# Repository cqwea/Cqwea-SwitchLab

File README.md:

# Cqwea SwitchLab

## About
cqwea switchlab is a calculator that does simple math problems and easy daily life problems as to why ive built it was I had enough with the other companies boring calculator designs and mushy buttons so ive built my own open case designed beautiful calculator with mechanic switches so its gonna be 10x better to press and do math at
## Features
MATH!
## Assembly

## Case

## Schematics

## PCB

## Aİ

Hey ima be honest i used ai to debug and make the placeholder code but the main code that ill srite when i got the device in hand is %100 hand written by me

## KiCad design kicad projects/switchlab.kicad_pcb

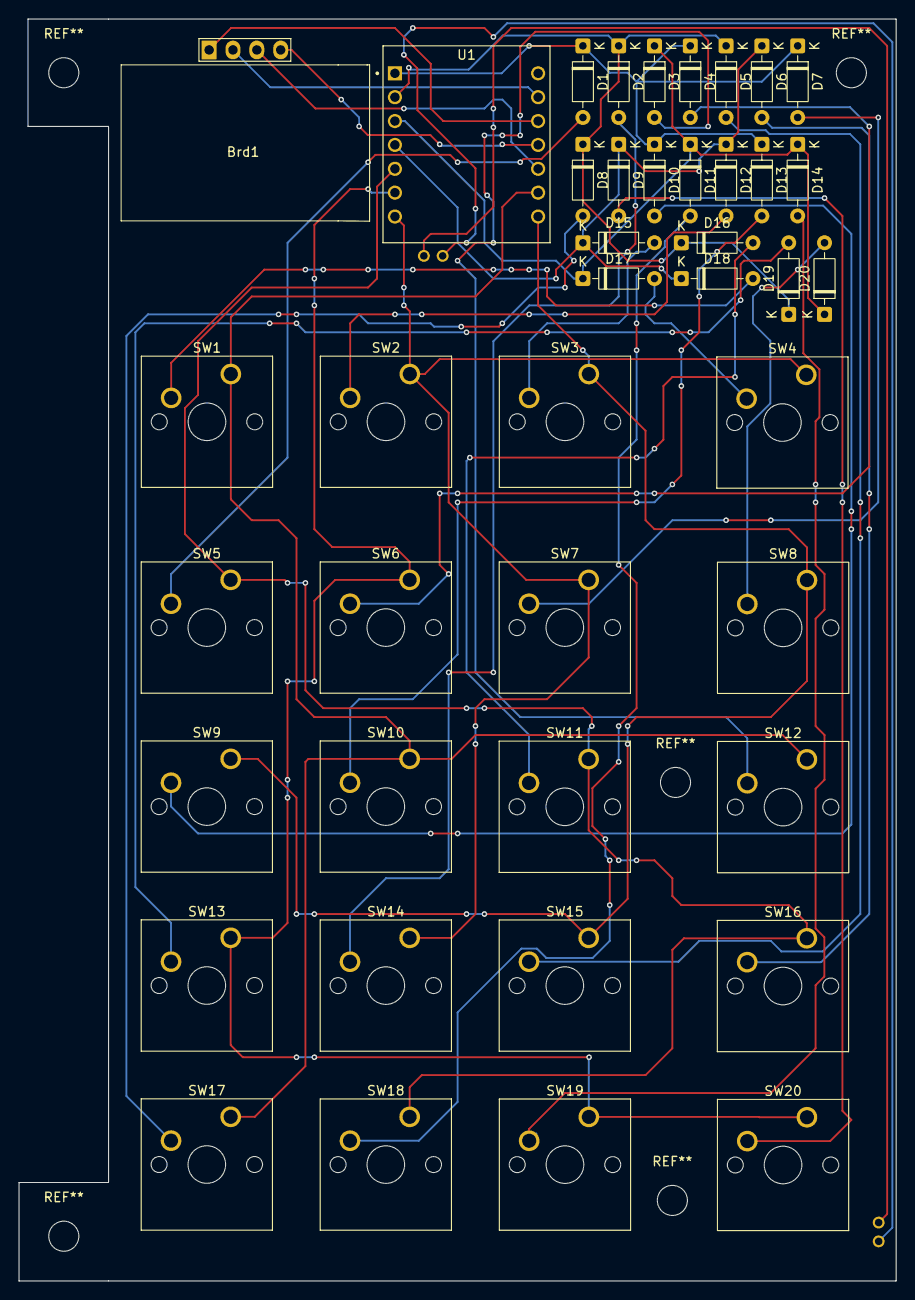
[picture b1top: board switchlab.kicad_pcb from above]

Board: 2 copper layers, 93.3 x 134.3 mm, 42 parts (0 on the bottom side), 33 nets.

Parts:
Brd1: SSD1306; 128x64OLED
D1, D2, D3, D4, D5, D6, D7, D8, D9, D10, D11, D12, D13, D14, D15, D16, D17, D18, D19, D20: 1N4148; D_DO-35_SOD27_P7.62mm_Horizontal
SW1, SW2, SW3, SW4, SW5, SW6, SW7, SW8, SW9, SW10, SW11, SW12, SW13, SW14, SW15, SW16, SW17, SW18, SW19, SW20: SW_Push; SW_Cherry_MX_1.00u_PCB
U1: XIAO_ESP32_S3; MODULE_XIAO_ESP32_S3

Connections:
/col1: SW5.1, SW11.1, SW16.1, SW18.1, U1.5 (D4/GPIO5)
/col2: SW6.1, SW13.1, SW19.1, SW20.1, U1.6 (D5/GPIO6)
/col3: SW2.1, SW4.1, SW7.1, SW14.1, U1.7 (D6/GPIO43)
/col4: SW3.1, SW8.1, SW9.1, SW15.1, U1.8 (D7/GPIO44)
/col5: SW1.1, SW10.1, SW12.1, SW17.1, U1.9 (D8/GPIO7)
/d7: Brd1.3 (SCL), U1.10 (D9/GPIO8)
/d8: Brd1.4 (SDA), U1.11 (D10/GPIO9)
/pwr: Brd1.1 (VCC), U1.12 (3V3)
/row1: D1.1 (K), D4.1 (K), D7.1 (K), D10.1 (K), D13.1 (K), U1.1 (D0/GPIO1)
/row2: D2.1 (K), D5.1 (K), D8.1 (K), D16.1 (K), D19.1 (K), U1.2 (D1/GPIO2)
/row3: D3.1 (K), D11.1 (K), D14.1 (K), D17.1 (K), D20.1 (K), U1.3 (D2/GPIO3)
/row4: D6.1 (K), D9.1 (K), D12.1 (K), D15.1 (K), D18.1 (K), U1.4 (D3/GPIO4)
GND: Brd1.2 (GND), U1.13 (GND)
unnamed: D1.2 (A), SW5.2
unnamed: D4.2 (A), SW6.2
unnamed: D7.2 (A), SW7.2
unnamed: D10.2 (A), SW9.2
unnamed: D13.2 (A), SW10.2
unnamed: D16.2 (A), SW11.2
unnamed: D19.2 (A), SW13.2
unnamed: D2.2 (A), SW14.2
unnamed: D5.2 (A), SW15.2
unnamed: D8.2 (A), SW17.2
unnamed: D11.2 (A), SW18.2
unnamed: D14.2 (A), SW19.2
unnamed: D17.2 (A), SW4.2
unnamed: D20.2 (A), SW8.2
unnamed: D3.2 (A), SW12.2
unnamed: D6.2 (A), SW16.2
unnamed: D9.2 (A), SW20.2
unnamed: D12.2 (A), SW2.2
unnamed: D15.2 (A), SW3.2
unnamed: D18.2 (A), SW1.2
